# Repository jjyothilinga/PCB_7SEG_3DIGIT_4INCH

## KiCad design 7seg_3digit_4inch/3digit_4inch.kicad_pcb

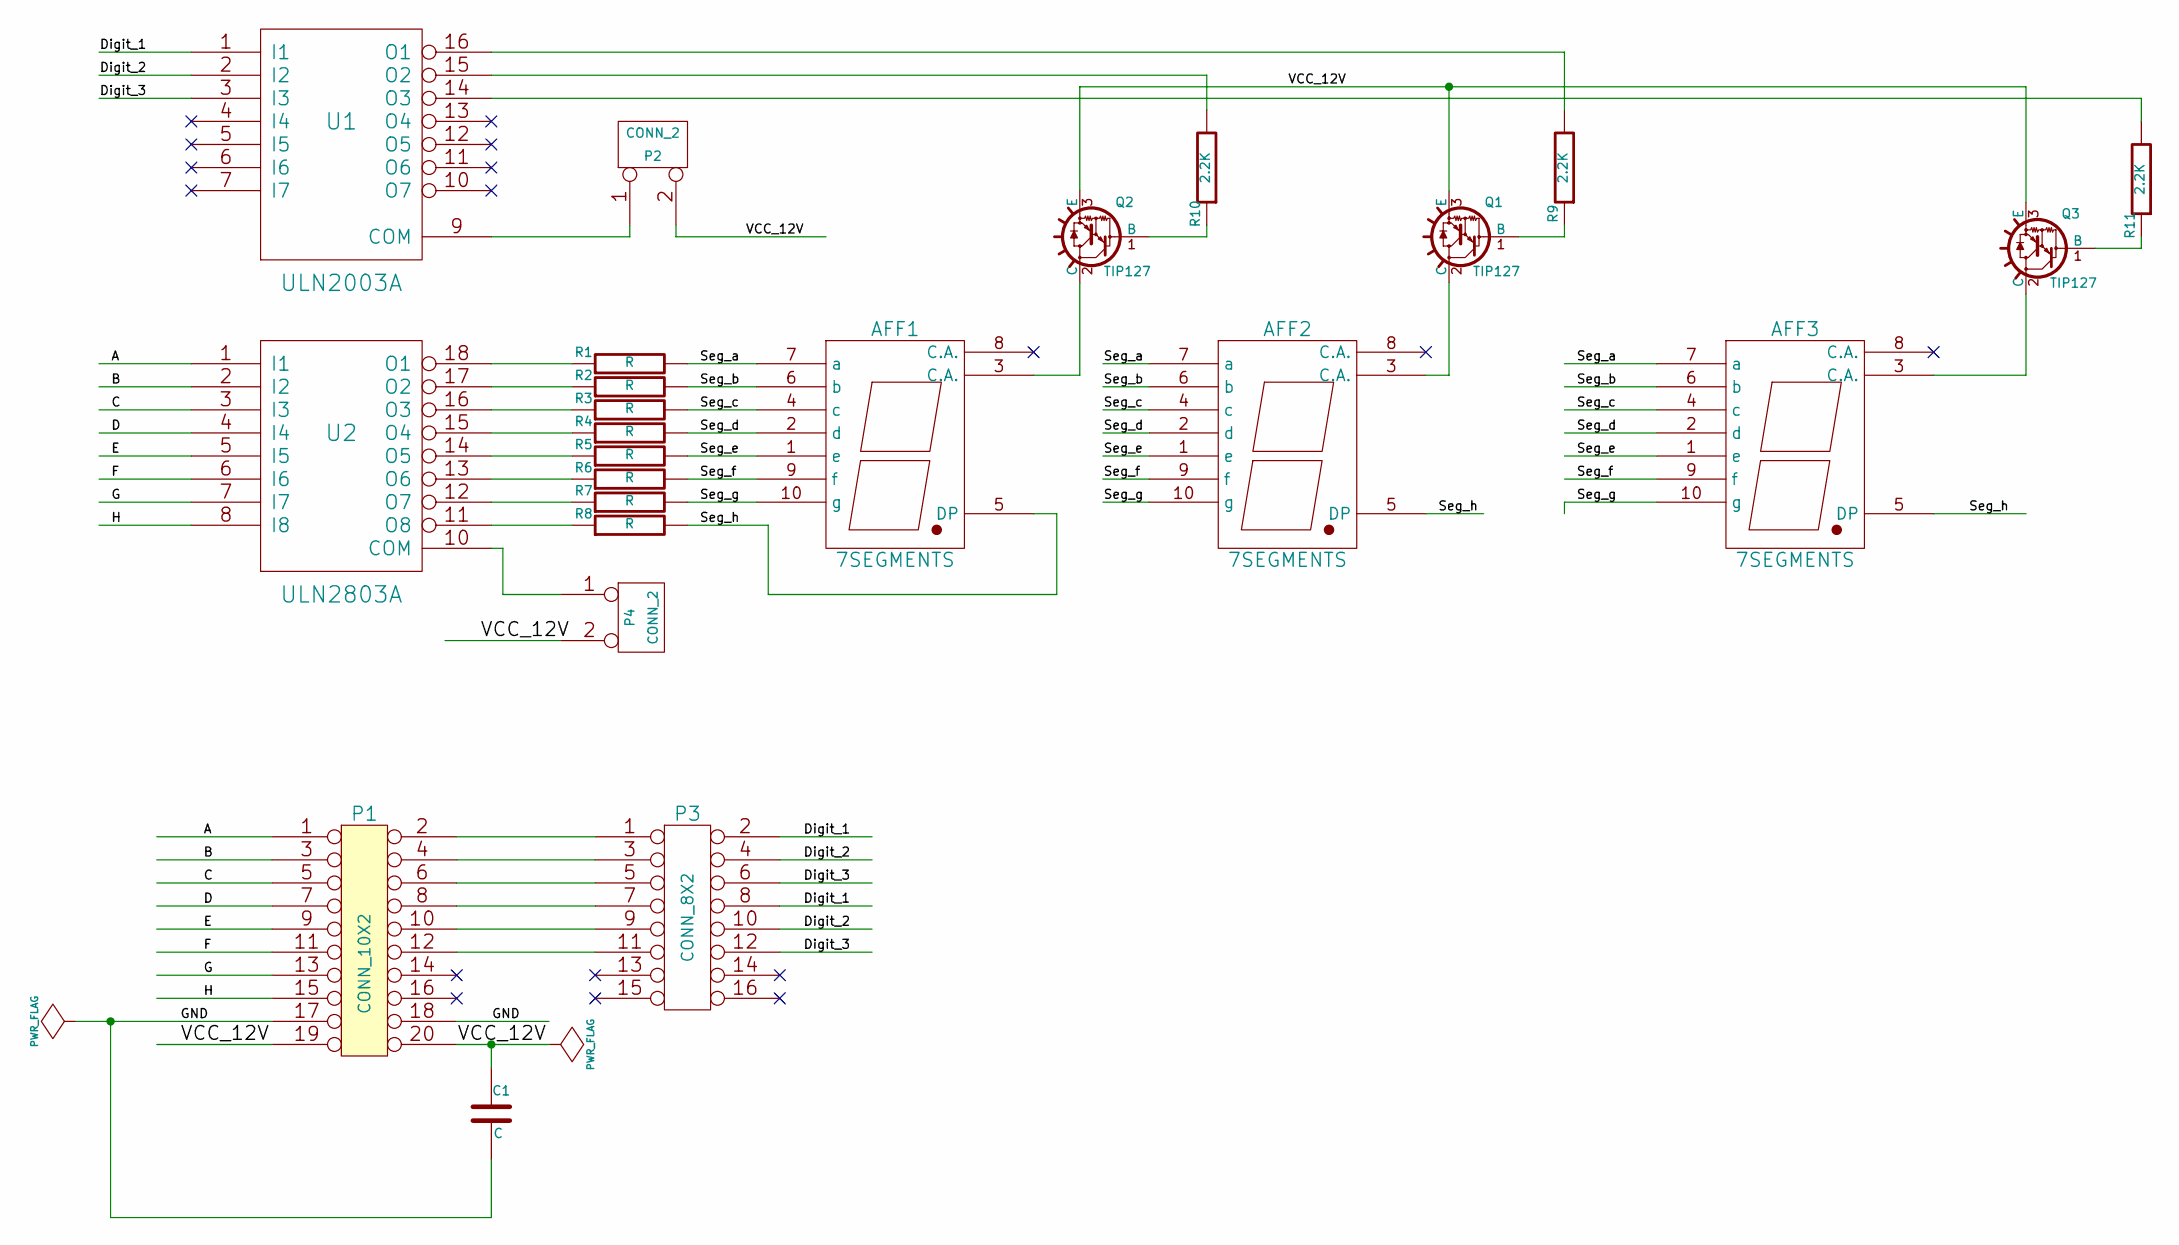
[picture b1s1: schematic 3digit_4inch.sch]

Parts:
AFF1, AFF2, AFF3: 7SEGMENTS
C1: C
P1: CONN_10X2
P2, P4: CONN_2
P3: CONN_8X2
Q1, Q2, Q3: TIP127; TO220
R1, R2, R3, R4, R5, R6, R7, R8: R
R9, R10, R11: 2.2K
U1: ULN2003A
U2: ULN2803A

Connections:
/A: P1.1, U2.1 (I1)
/B: P1.3, U2.2 (I2)
/C: P1.5, U2.3 (I3)
/D: P1.7, U2.4 (I4)
/Digit_1: P3.2, P3.8, U1.1 (I1)
/Digit_2: P3.4, P3.10, U1.2 (I2)
/Digit_3: P3.6, P3.12, U1.3 (I3)
/E: P1.9, U2.5 (I5)
/F: P1.11, U2.6 (I6)
/G: P1.13, U2.7 (I7)
/H: P1.15, U2.8 (I8)
/Seg_a: AFF1.7 (a), AFF2.7 (a), AFF3.7 (a), R1.2
/Seg_b: AFF1.6 (b), AFF2.6 (b), AFF3.6 (b), R2.2
/Seg_c: AFF1.4 (c), AFF2.4 (c), AFF3.4 (c), R3.2
/Seg_d: AFF1.2 (d), AFF2.2 (d), AFF3.2 (d), R4.2
/Seg_e: AFF1.1 (e), AFF2.1 (e), AFF3.1 (e), R5.2
/Seg_f: AFF1.9 (f), AFF2.9 (f), AFF3.9 (f), R6.2
/Seg_g: AFF1.10 (g), AFF2.10 (g), AFF3.10 (g), R7.2
/Seg_h: AFF1.5 (DP), AFF2.5 (DP), AFF3.5 (DP), R8.2
/VCC_12V: C1.1, P1.19, P1.20, P2.2 (PM), P4.2 (PM), Q1.3 (E), Q2.3 (E), Q3.3 (E)
GND: C1.2, P1.17, P1.18, U1.8 (GND), U2.9 (GND)
unnamed: Q1.1 (B), R9.1
unnamed: Q2.1 (B), R10.1
unnamed: R9.2, U1.16 (O1)
unnamed: R6.1, U2.13 (O6)
unnamed: P4.1, U2.10 (COM)
unnamed: R1.1, U2.18 (O1)
unnamed: R2.1, U2.17 (O2)
unnamed: R3.1, U2.16 (O3)
unnamed: R4.1, U2.15 (O4)
unnamed: R5.1, U2.14 (O5)
unnamed: R7.1, U2.12 (O7)
unnamed: R8.1, U2.11 (O8)
unnamed: P1.12, P3.11
unnamed: P1.10, P3.9
unnamed: P1.8, P3.7
unnamed: P1.6, P3.5
unnamed: P1.4, P3.3
unnamed: P1.2, P3.1
unnamed: AFF2.3 (C.A.), Q1.2 (C)
unnamed: P2.1, U1.9 (COM)
unnamed: R10.2, U1.15 (O2)
unnamed: AFF1.3 (C.A.), Q2.2 (C)
unnamed: AFF3.3 (C.A.), Q3.2 (C)
unnamed: R11.2, U1.14 (O3)
unnamed: Q3.1 (B), R11.1

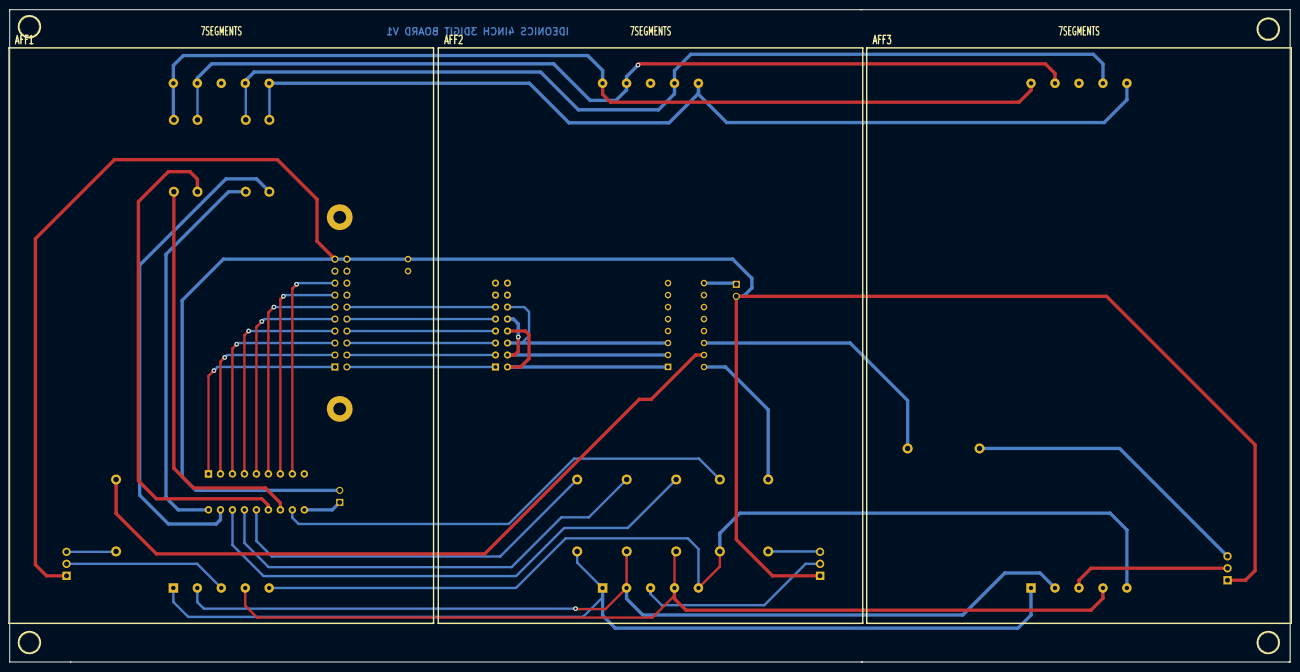
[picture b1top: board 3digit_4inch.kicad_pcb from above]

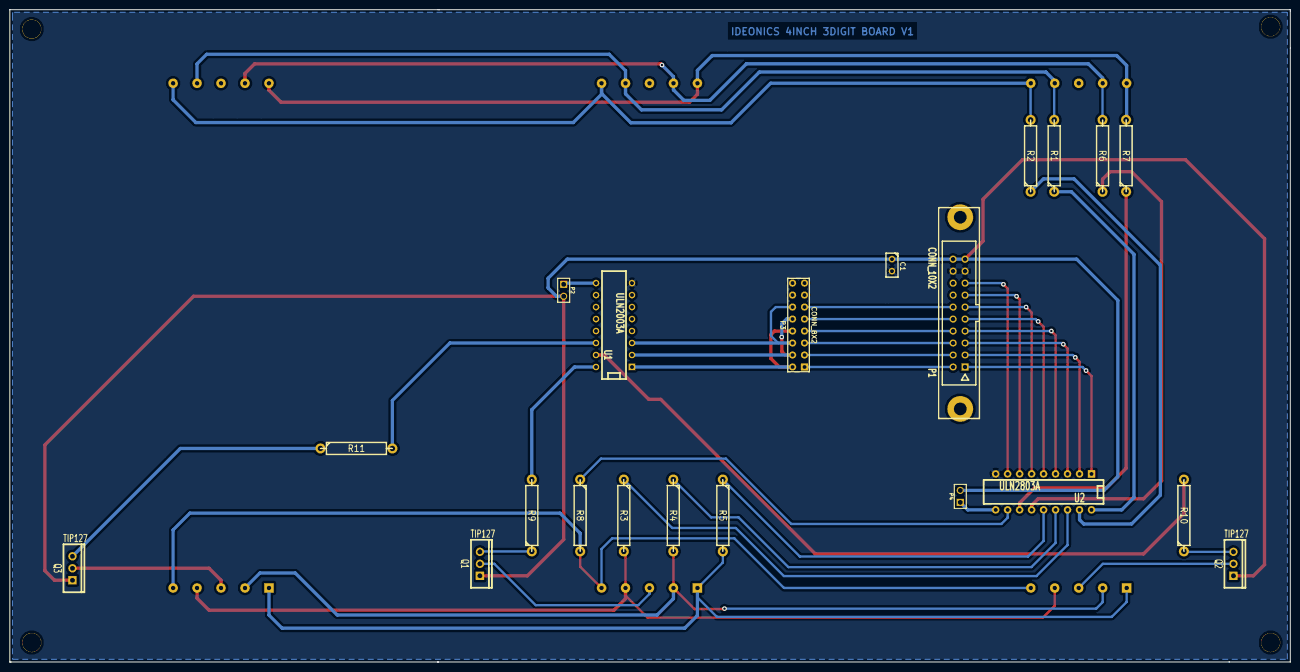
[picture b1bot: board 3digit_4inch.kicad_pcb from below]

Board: 2 copper layers, 271.5 x 138.3 mm, 28 parts (21 on the bottom side), 46 nets.

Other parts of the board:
1PIN, 1PIN#2, 1PIN#3, 1PIN#4: P***; 1pin

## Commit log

2015-06-09 :confetti_ball: Added .gitattributes & .gitignore files
2015-06-09 Completed
